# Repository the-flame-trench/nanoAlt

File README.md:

# nanoAlt
This repo contains the open source hardware and software for [The Flame Trench](http://theflametrench.com)'s nanoAlt nano-scale rocketry altimeter family.

The project is not currently being prioritised, but we hope to be able to make nanoAlt Alpha available in kit form soon.

## nanoAlt Alpha
nanoAlt Alpha is the base version of the altimeter, using an ATTiny24A and simple barometer.  It is powered via 4.8mm coin cell, and reports altitude readings via flashing LED.  The software for nanoAlt Alpha is in an early state of development owing to the delays in finalising assembly for the boards, and is therefore unpublished at this time.  The nanoAlt Alpha boards expose a set of programming pins to allow custom programming of the microcontroller.

## nanoAlt Integrate
nanoAlt Integrate is a series of fittings designed to mount the nanoAlt family in a variety of common rocketry tube diameters.  Currently a BT-5 test piece is published, owing to the nanoAlt Alpha initially being designed for very small minimum diameter builds.

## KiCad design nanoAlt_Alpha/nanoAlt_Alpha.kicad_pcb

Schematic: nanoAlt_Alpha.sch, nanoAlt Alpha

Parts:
C1, C2: 100n; C_0402_1005Metric
D1: LED; LED_0402_1005Metric
IC1: MS563702BA03-50; MS5637_1; Manufacturer_Part_Number MS563702BA03-50
J1: AVR_SPI_PROG_3X2TESTPOINTS; 50mil_POGO
R1, R2, R3: 10K; R_0402_1005Metric
R4: 33; R_0402_1005Metric
U1: ATtiny24A-CCU; UFBGA-15_3.0x3.0mm_Layout4x4_P0.65mm

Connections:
+BATT: C1.1, C2.1, IC1.1, J1.2 (VCC), R1.1, R2.1, R3.1, U1.D4; also elsewhere on the board
/MISO: J1.1 (MISO), U1.A2
/MOSI: IC1.2, J1.4 (MOSI), R2.2, U1.A3
/RST: J1.5 (RST), R1.2, U1.B4
/SCL: IC1.3, J1.3 (SCK), R3.2, U1.B1
GND: C1.2, C2.2, D1.1, IC1.4, J1.6 (GND), U1.D2, U1.D3; also elsewhere on the board
unnamed: D1.2, R4.2
unnamed: R4.1, U1.D1

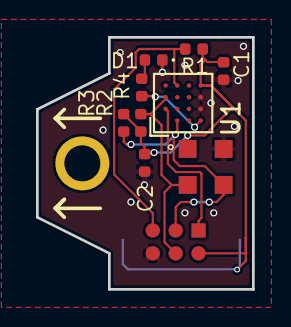
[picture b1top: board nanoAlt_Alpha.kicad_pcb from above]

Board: 2 copper layers, 12.0 x 14.0 mm, 12 parts (1 on the bottom side), 8 nets.

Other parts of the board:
BATT_3V: Keystone2994_4.8mm_coincellholder
INTEGRATE: 2mm_hole

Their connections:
+BATT: BATT_3V.1; also elsewhere on the board
GND: BATT_3V.2; also elsewhere on the board

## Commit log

2019-10-23 repo base files upload
2019-10-23 initial CAD file upload
2019-10-23 readme added
2019-10-23 project should now open from rescued cache
2020-01-07 Update README.md
    fixed TFT link
2020-05-20 Update LICENSE to CERN OHLv2-s
2020-05-20 Remove gerber files from repo
2020-05-21 Fix ERC issues on schematic and update library
2020-05-21 Reroute for 2 layers
